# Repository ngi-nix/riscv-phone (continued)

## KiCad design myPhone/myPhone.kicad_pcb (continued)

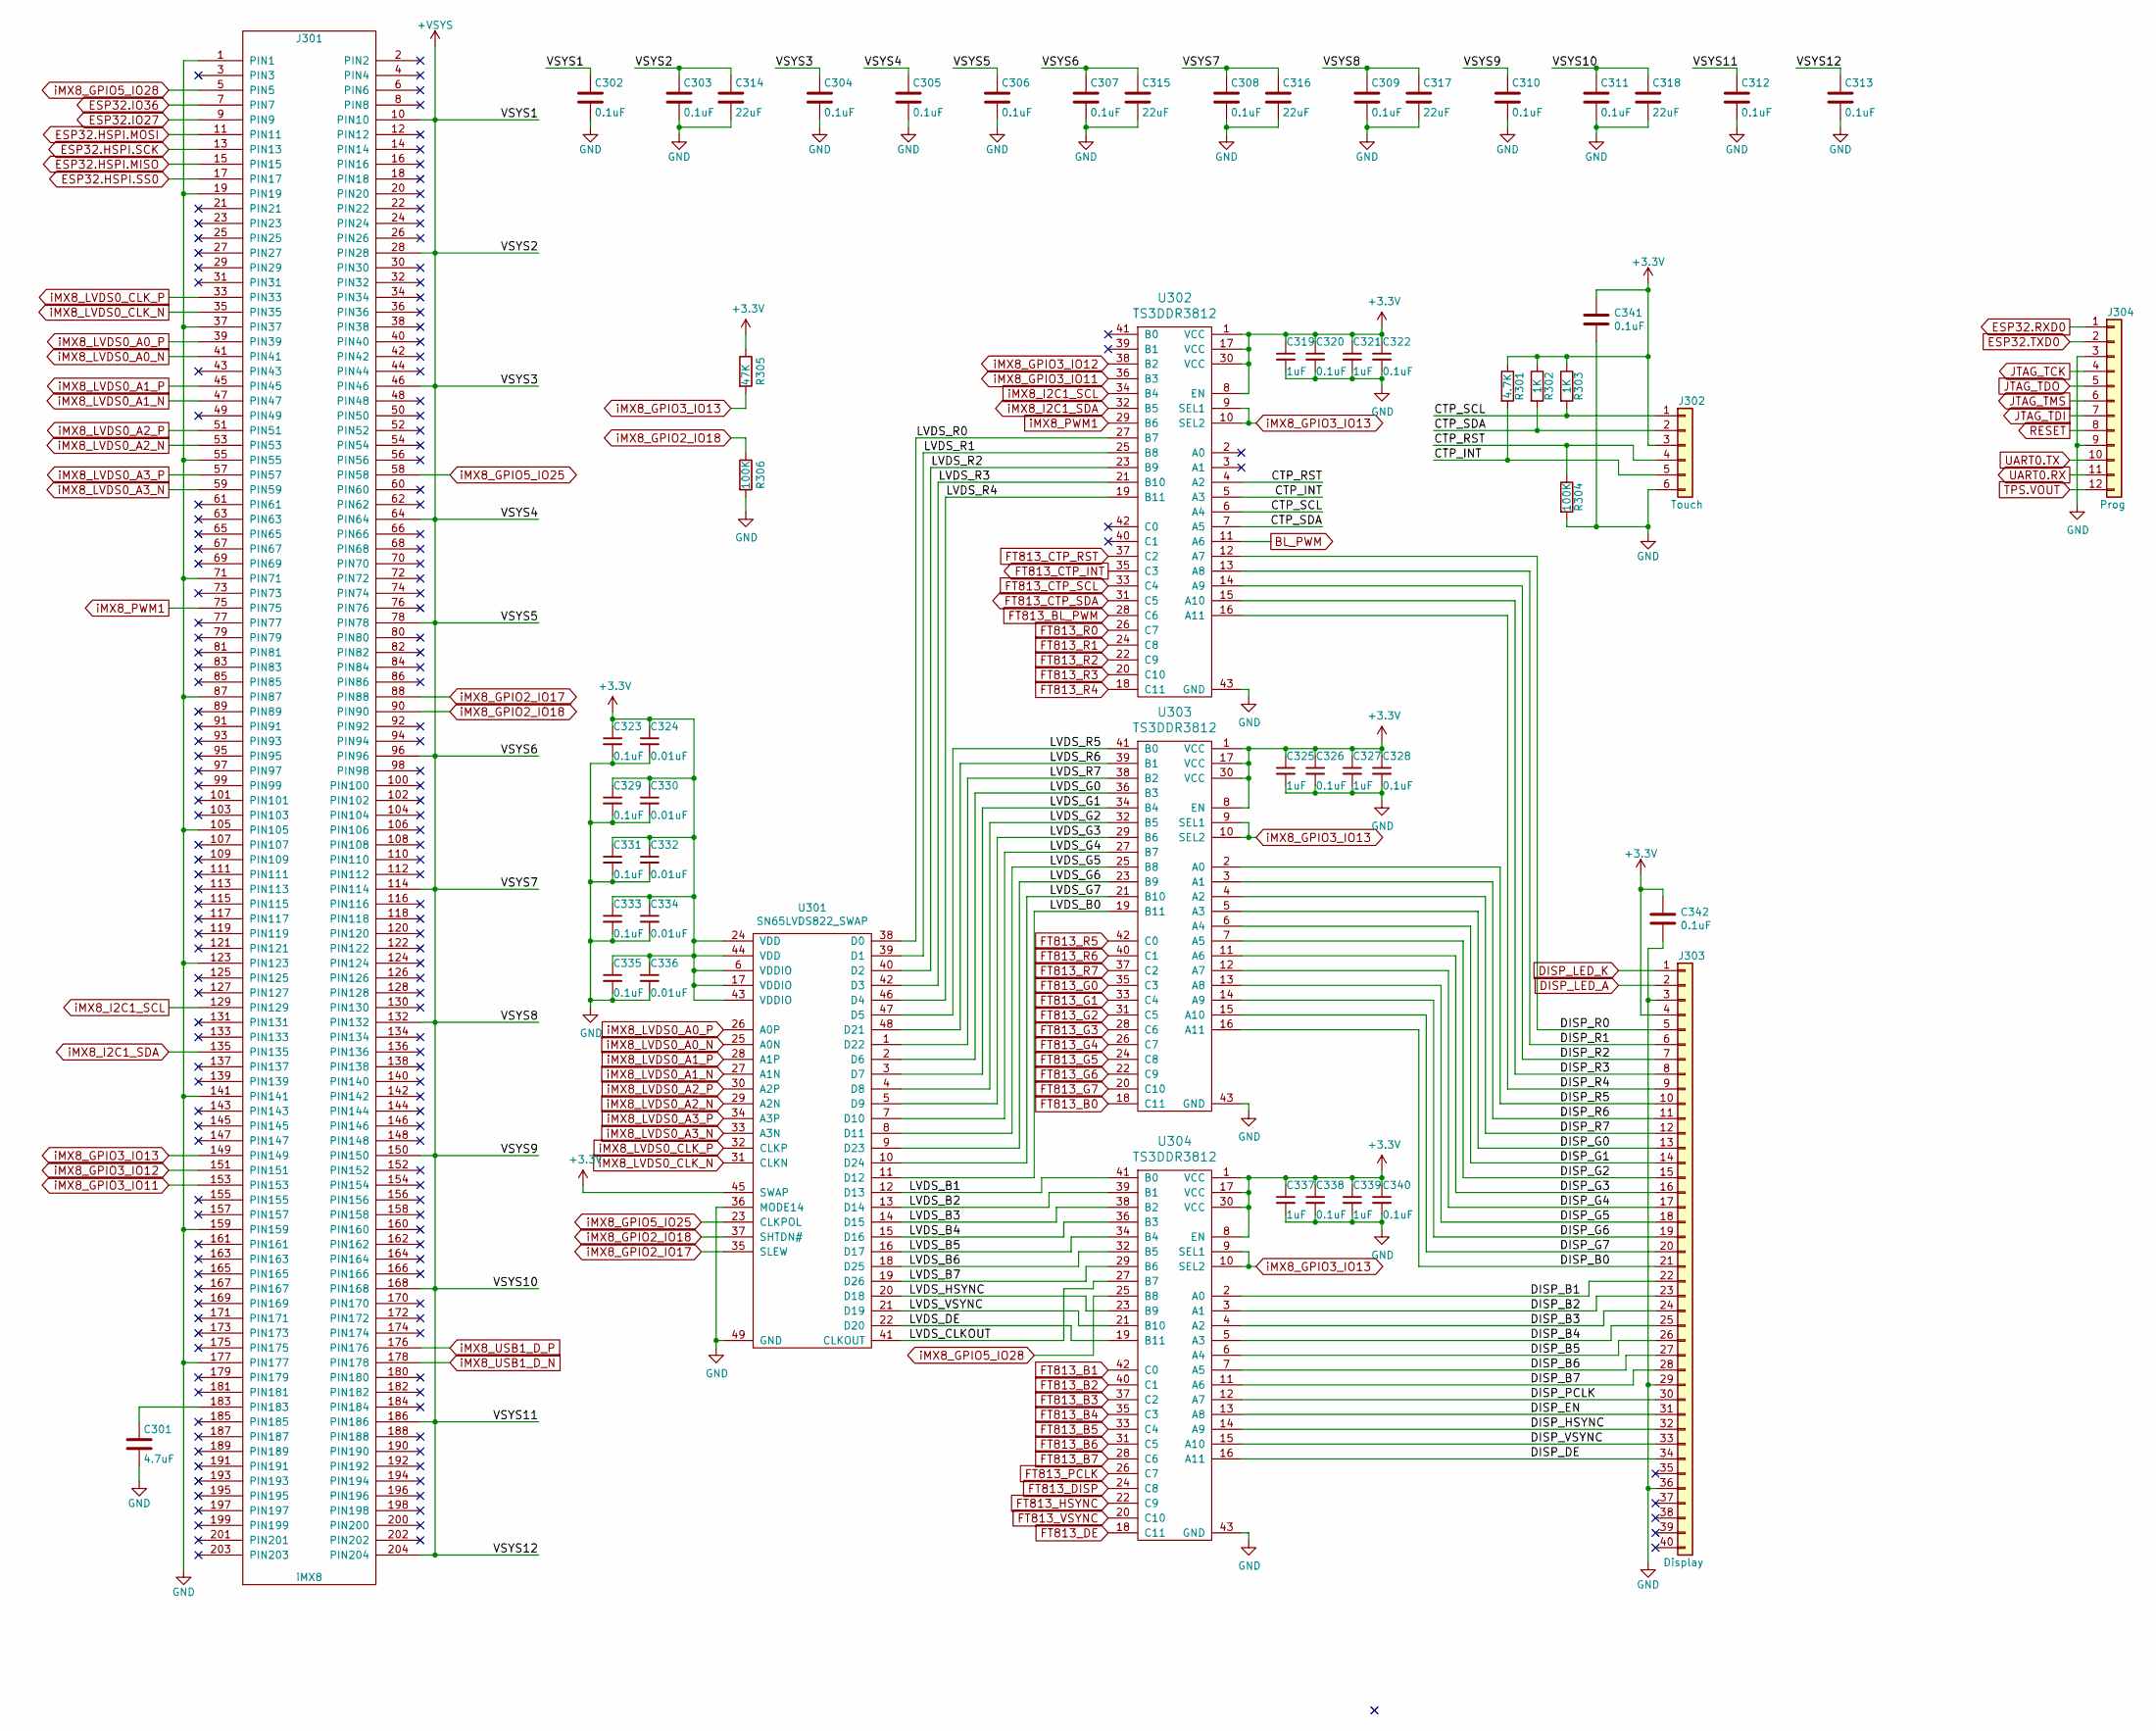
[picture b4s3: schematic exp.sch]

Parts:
C301: 4.7uF; C_0603_1608Metric
C302, C303, C304, C305, C306, C307, C308, C309, C310, C311, C312, C313, C320, C322, C323, C326, C328, C329, C331, C333, C335, C338, C340, C341, C342: 0.1uF; C_0603_1608Metric
C314, C315, C316, C317, C318: 22uF; C_0603_1608Metric
C319, C321, C325, C327, C337, C339: 1uF; C_0603_1608Metric
C324, C330, C332, C334, C336: 0.01uF; C_0603_1608Metric
J301: iMX8; Socket_SODIMM_DDR3_TE_2013289
J302: Touch; Hirose_FH12-6S-0.5SH_1x06-1MP_P0.50mm_Horizontal
J303: Display; Hirose_FH12-40S-0.5SH_1x40-1MP_P0.50mm_Horizontal
J304: Prog; Hirose_FH12-12S-0.5SH_1x12-1MP_P0.50mm_Horizontal
R301: 4.7K; R_0603_1608Metric
R302, R303: 1K; R_0603_1608Metric
R304, R306: 100K; R_0603_1608Metric
R305: 47K; R_0603_1608Metric
U301: SN65LVDS822_SWAP; QFN-48-1EP_7x7mm_P0.5mm_EP5.15x5.15mm_ThermalVias
U302, U303, U304: TS3DDR3812; Texas_R-PWQFN-N42

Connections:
+VSYS: C302.1, C303.1, C304.1, C305.1, C306.1, C307.1, C308.1, C309.1, C310.1, C311.1, C312.1, C313.1, C314.1, C315.1, C316.1, C317.1, C318.1, J301.10 (PIN10), J301.28 (PIN28), J301.46 (PIN46), J301.64 (PIN64), J301.78 (PIN78), J301.96 (PIN96), J301.114 (PIN114), J301.132 (PIN132), J301.150 (PIN150), J301.168 (PIN168), J301.186 (PIN186), J301.204 (PIN204); also elsewhere on the board
/exp/CTP_INT: J302.5, R301.2, U302.5 (A3)
/exp/CTP_RST: J302.4, R304.1, U302.4 (A2)
/exp/CTP_SCL: J302.1, R303.2, U302.6 (A4)
/exp/CTP_SDA: J302.2, R302.2, U302.7 (A5)
/exp/DISP_B0: J303.21, U303.16 (A11)
/exp/DISP_B1: J303.22, U304.2 (A0)
/exp/DISP_B2: J303.23, U304.3 (A1)
/exp/DISP_B3: J303.24, U304.4 (A2)
/exp/DISP_B4: J303.25, U304.5 (A3)
/exp/DISP_B5: J303.26, U304.6 (A4)
/exp/DISP_B6: J303.27, U304.7 (A5)
/exp/DISP_B7: J303.28, U304.11 (A6)
/exp/DISP_DE: J303.34, U304.16 (A11)
/exp/DISP_EN: J303.31, U304.13 (A8)
/exp/DISP_G0: J303.13, U303.5 (A3)
/exp/DISP_G1: J303.14, U303.6 (A4)
/exp/DISP_G2: J303.15, U303.7 (A5)
/exp/DISP_G3: J303.16, U303.11 (A6)
/exp/DISP_G4: J303.17, U303.12 (A7)
/exp/DISP_G5: J303.18, U303.13 (A8)
/exp/DISP_G6: J303.19, U303.14 (A9)
/exp/DISP_G7: J303.20, U303.15 (A10)
/exp/DISP_HSYNC: J303.32, U304.14 (A9)
/exp/DISP_PCLK: J303.30, U304.12 (A7)
/exp/DISP_R0: J303.5, U302.12 (A7)
/exp/DISP_R1: J303.6, U302.13 (A8)
/exp/DISP_R2: J303.7, U302.14 (A9)
/exp/DISP_R3: J303.8, U302.15 (A10)
/exp/DISP_R4: J303.9, U302.16 (A11)
/exp/DISP_R5: J303.10, U303.2 (A0)
/exp/DISP_R6: J303.11, U303.3 (A1)
/exp/DISP_R7: J303.12, U303.4 (A2)
/exp/DISP_VSYNC: J303.33, U304.15 (A10)
/exp/LVDS_B0: U301.11 (D12), U303.19 (B11)
/exp/LVDS_B1: U301.12 (D13), U304.41 (B0)
/exp/LVDS_B2: U301.13 (D14), U304.39 (B1)
/exp/LVDS_B3: U301.14 (D15), U304.38 (B2)
/exp/LVDS_B4: U301.15 (D16), U304.36 (B3)
/exp/LVDS_B5: U301.16 (D17), U304.34 (B4)
/exp/LVDS_B6: U301.18 (D25), U304.32 (B5)
/exp/LVDS_B7: U301.19 (D26), U304.29 (B6)
/exp/LVDS_CLKOUT: U301.41 (CLKOUT), U304.27 (B7)
/exp/LVDS_DE: U301.22 (D20), U304.19 (B11)
/exp/LVDS_G0: U301.2 (D6), U303.36 (B3)
/exp/LVDS_G1: U301.3 (D7), U303.34 (B4)
/exp/LVDS_G2: U301.4 (D8), U303.32 (B5)
/exp/LVDS_G3: U301.5 (D9), U303.29 (B6)
/exp/LVDS_G4: U301.7 (D10), U303.27 (B7)
/exp/LVDS_G5: U301.8 (D11), U303.25 (B8)
/exp/LVDS_G6: U301.9 (D23), U303.23 (B9)
/exp/LVDS_G7: U301.10 (D24), U303.21 (B10)
/exp/LVDS_HSYNC: U301.20 (D18), U304.23 (B9)
/exp/LVDS_R0: U301.38 (D0), U302.27 (B7)
/exp/LVDS_R1: U301.39 (D1), U302.25 (B8)
/exp/LVDS_R2: U301.40 (D2), U302.23 (B9)
/exp/LVDS_R3: U301.42 (D3), U302.21 (B10)
/exp/LVDS_R4: U301.46 (D4), U302.19 (B11)
/exp/LVDS_R5: U301.47 (D5), U303.41 (B0)
/exp/LVDS_R6: U301.48 (D21), U303.39 (B1)
/exp/LVDS_R7: U301.1 (D22), U303.38 (B2)
/exp/LVDS_VSYNC: U301.21 (D19), U304.21 (B10)
BL_PWM: U302.11 (A6); also elsewhere on the board
DISP_LED_A: J303.2; also elsewhere on the board
DISP_LED_K: J303.1; also elsewhere on the board
ESP32.HSPI.MISO: J301.15 (PIN15); also elsewhere on the board
ESP32.HSPI.MOSI: J301.11 (PIN11); also elsewhere on the board
ESP32.HSPI.SCK: J301.13 (PIN13); also elsewhere on the board
ESP32.HSPI.SS0: J301.17 (PIN17); also elsewhere on the board
ESP32.IO27: J301.9 (PIN9); also elsewhere on the board
ESP32.IO36: J301.7 (PIN7); also elsewhere on the board
ESP32.RXD0: J304.1; also elsewhere on the board
ESP32.TXD0: J304.2; also elsewhere on the board
FT813_B0: U303.18 (C11); also elsewhere on the board
FT813_B1: U304.42 (C0); also elsewhere on the board
FT813_B2: U304.40 (C1); also elsewhere on the board
FT813_B3: U304.37 (C2); also elsewhere on the board
FT813_B4: U304.35 (C3); also elsewhere on the board
FT813_B5: U304.33 (C4); also elsewhere on the board
FT813_B6: U304.31 (C5); also elsewhere on the board
FT813_B7: U304.28 (C6); also elsewhere on the board
FT813_BL_PWM: U302.28 (C6); also elsewhere on the board
FT813_CTP_INT: U302.35 (C3); also elsewhere on the board
FT813_CTP_RST: U302.37 (C2); also elsewhere on the board
FT813_CTP_SCL: U302.33 (C4); also elsewhere on the board
FT813_CTP_SDA: U302.31 (C5); also elsewhere on the board
FT813_DE: U304.18 (C11); also elsewhere on the board
FT813_DISP: U304.24 (C8); also elsewhere on the board
FT813_G0: U303.35 (C3); also elsewhere on the board
FT813_G1: U303.33 (C4); also elsewhere on the board
FT813_G2: U303.31 (C5); also elsewhere on the board
FT813_G3: U303.28 (C6); also elsewhere on the board
FT813_G4: U303.26 (C7); also elsewhere on the board
FT813_G5: U303.24 (C8); also elsewhere on the board
FT813_G6: U303.22 (C9); also elsewhere on the board
FT813_G7: U303.20 (C10); also elsewhere on the board
FT813_HSYNC: U304.22 (C9); also elsewhere on the board
FT813_PCLK: U304.26 (C7); also elsewhere on the board
FT813_R0: U302.26 (C7); also elsewhere on the board
FT813_R1: U302.24 (C8); also elsewhere on the board
FT813_R2: U302.22 (C9); also elsewhere on the board
FT813_R3: U302.20 (C10); also elsewhere on the board
FT813_R4: U302.18 (C11); also elsewhere on the board
FT813_R5: U303.42 (C0); also elsewhere on the board
FT813_R6: U303.40 (C1); also elsewhere on the board
FT813_R7: U303.37 (C2); also elsewhere on the board
FT813_VSYNC: U304.20 (C10); also elsewhere on the board
GND: C301.2, C302.2, C303.2, C304.2, C305.2, C306.2, C307.2, C308.2, C309.2, C310.2, C311.2, C312.2, C313.2, C314.2, C315.2, C316.2, C317.2, C318.2, C319.2, C320.2, C321.2, C322.2, C323.2, C324.2, C325.2, C326.2, C327.2, C328.2, C329.2, C330.2, C331.2, C332.2, C333.2, C334.2, C335.2, C336.2, C337.2, C338.2, C339.2, C340.2, C341.2, C342.2, J301.1 (PIN1), J301.19 (PIN19), J301.37 (PIN37), J301.55 (PIN55), J301.71 (PIN71), J301.87 (PIN87), J301.105 (PIN105), J301.123 (PIN123), J301.141 (PIN141), J301.159 (PIN159), J301.177 (PIN177), J302.6, J303.3, J303.29, J303.36, J304.3, J304.9, R304.2, R306.2, U301.36 (MODE14), U301.49 (GND), U302.43 (GND), U303.43 (GND), U304.43 (GND); also elsewhere on the board
JTAG_TCK: J304.4; also elsewhere on the board
JTAG_TDI: J304.7; also elsewhere on the board
JTAG_TDO: J304.5; also elsewhere on the board
JTAG_TMS: J304.6; also elsewhere on the board
unnamed: C301.1, J301.183 (PIN183)
RESET: J304.8; also elsewhere on the board
TPS.VOUT: J304.12; also elsewhere on the board
UART0.RX: J304.11; also elsewhere on the board
UART0.TX: J304.10; also elsewhere on the board
iMX8_GPIO2_IO17: J301.88 (PIN88), U301.35 (SLEW)
iMX8_GPIO2_IO18: J301.90 (PIN90), R306.1, U301.37 (SHTDN#)
iMX8_GPIO3_IO11: J301.153 (PIN153), U302.36 (B3)
iMX8_GPIO3_IO12: J301.151 (PIN151), U302.38 (B2)
iMX8_GPIO3_IO13: J301.149 (PIN149), R305.2, U302.9 (SEL1), U302.10 (SEL2), U303.9 (SEL1), U303.10 (SEL2), U304.9 (SEL1), U304.10 (SEL2)
iMX8_GPIO5_IO25: J301.58 (PIN58), U301.23 (CLKPOL)
iMX8_GPIO5_IO28: J301.5 (PIN5), U304.25 (B8)
iMX8_I2C1_SCL: J301.129 (PIN129), U302.34 (B4)
iMX8_I2C1_SDA: J301.135 (PIN135), U302.32 (B5)
iMX8_LVDS0_A0_N: J301.41 (PIN41), U301.25 (A0N)
iMX8_LVDS0_A0_P: J301.39 (PIN39), U301.26 (A0P)
iMX8_LVDS0_A1_N: J301.47 (PIN47), U301.27 (A1N)
iMX8_LVDS0_A1_P: J301.45 (PIN45), U301.28 (A1P)
iMX8_LVDS0_A2_N: J301.53 (PIN53), U301.29 (A2N)
iMX8_LVDS0_A2_P: J301.51 (PIN51), U301.30 (A2P)
iMX8_LVDS0_A3_N: J301.59 (PIN59), U301.33 (A3N)
iMX8_LVDS0_A3_P: J301.57 (PIN57), U301.34 (A3P)
iMX8_LVDS0_CLK_N: J301.35 (PIN35), U301.31 (CLKN)
iMX8_LVDS0_CLK_P: J301.33 (PIN33), U301.32 (CLKP)
iMX8_PWM1: J301.75 (PIN75), U302.29 (B6)
iMX8_USB1_D_N: J301.178 (PIN178); also elsewhere on the board
iMX8_USB1_D_P: J301.176 (PIN176); also elsewhere on the board

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
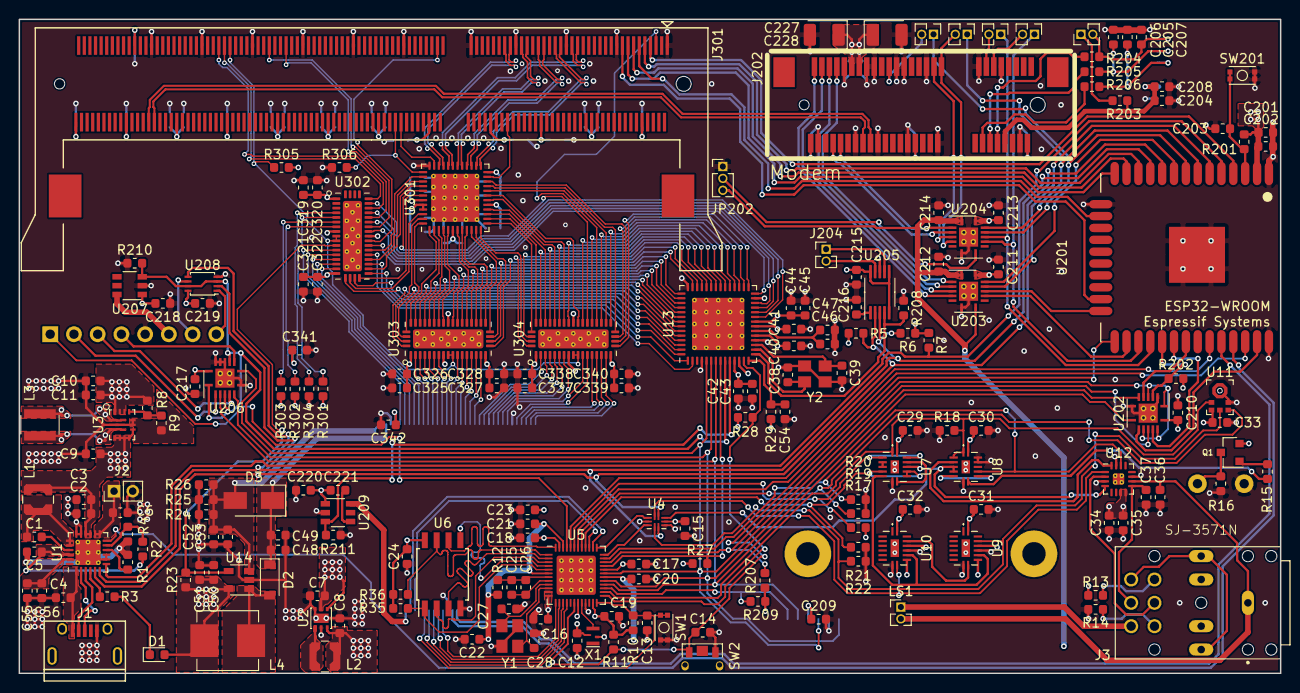
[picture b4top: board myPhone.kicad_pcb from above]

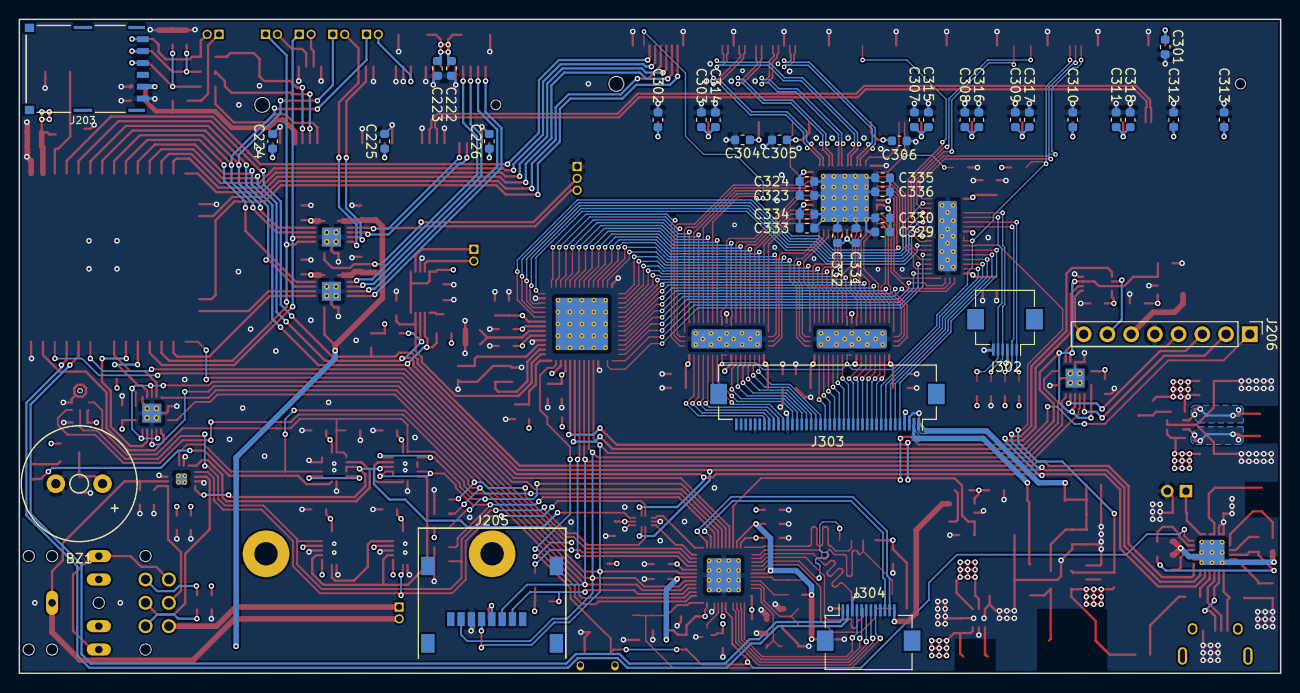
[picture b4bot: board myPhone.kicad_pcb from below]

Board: 4 copper layers, 135.0 x 70.0 mm, 235 parts (40 on the bottom side), 259 nets.

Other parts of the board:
C15: 0.1uF; C_0603_1608Metric
C55, C56: 22uF; C_0603_1608Metric
U4: TMUX154E; UQFN-10_1.3x1.8mm_P0.4mm

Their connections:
/SPK_EN: U4.10; also elsewhere on the board
GND: C15.2, C55.2, C56.2, U4.4, U4.8; also elsewhere on the board
unnamed 176: C55.1, C56.1; also elsewhere on the board
TMUX.I2C0.SCL: U4.1; also elsewhere on the board
TMUX.I2C0.SDA: U4.7; also elsewhere on the board

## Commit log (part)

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2020-02-26 ecp/eos new compatibility changes
2020-02-26 spidev set divider
2020-02-26 fixed build system
2020-02-26 text widget added, NOT TESTED
2020-03-07 fixed sbrk
2020-03-07 eve screen/tile/canvas/page/form fw added; page widget added
2020-03-07 fixed build sys
2020-03-11 timer fix
2020-05-06 at cmd processing; pppos driver
2020-05-09 added sleep/wake for modem; fixed ppp driver API
2020-05-09 fixed wifi driver
2020-05-09 wifi driver fix
2020-05-17 power management implemented; net protocol change
2020-05-17 power management fix
2020-05-18 poer management fix
2020-05-23 esp32 deep sleep implemented
2020-05-26 added license
2020-05-26 added license files
2020-06-06 ecp_timer_retry_t typedef fixed
2020-06-06 ecp_conn_handler_new_t typedef fixed
2020-06-06 ecp_conn_handler_msg_t typedef fixed
2020-06-06 ecp_conn_alloc_t/ecp_conn_free_t typedefs fixed
2020-06-06 ecp_conn_create_t/ecp_conn_destroy_t/ecp_conn_open_t/ecp_conn_close_t typedefs fixed
2020-06-08 touch extended tracking refactor
2020-06-08 kbd iface fixed
2020-06-08 EVEView iface fixed; screen keyboard window implemented
2020-06-11 added widget labels
2020-06-11 implemented font metrics
2020-06-25 extendend events implemented for touch
2020-06-25 text widget fixed
2020-07-02 string widget implemented
2020-07-02 string init/draw implemented; page to screen coordinates implemented
2020-07-03 str widget draw selection and cursor implemented
2020-07-11 screen/window/kbd window implemented; str widget tested
2020-07-11 kbdwin source added
2020-07-11 page focus interface changed; widget is responsible for setting focus
2020-07-11 String copy/paste implemented
2020-08-03 unicode verify fixed
2020-08-03 unicode moved
2020-08-04 added tmux lib
2020-08-04 renamed to rvPhone
2020-08-05 unicode seek fix
2020-08-05 cell message type support
2020-08-05 new directory sructure for fe310 fw
2020-08-05 cell urc buffer handling fixed; added sms/ussd/voice/data stubs
2020-08-05 unicode support added
2020-08-05 ecp moved to root; fixed utils and tests
2020-08-05 code -> fw
2020-08-05 fixed modem test example
2020-08-07 net driver: removed obsolete flags; urc process simplefied; pcm: added active flag; tested cell voice/data
2020-08-07 added cell message types
2020-08-09 sms service added/tested
2020-08-09 unicode utf_len added; cell sms services added
2020-08-09 message handling iface updated
2020-08-09 uart dirty property added
2020-08-09 sms send wait for prompt
2020-08-09 added new sms flags
2020-08-09 sms storage flash mem
2020-08-09 support for sms flags
2020-08-11 cell messages are handled in separate task
2020-08-23 dynamic memory alloc for gui added; page navigation added
2020-08-24 fixed bug in form constructor; free widget improved
2020-08-26 display list burst mode added
2020-08-26 kbdwin removed; stack and contructor moved to view
2020-08-26 modem test application appified
2020-12-04 stereo audio out; lvds display; LSM9DS1 added
2021-02-24 i2c driver initial import
2021-02-24 added test app with voice, wifi/cellular data connectivity examples
2021-02-24 upgraded to esp-idf 4.2
2021-02-26 widgets are excluded from touch events when form gesture is in progress
2021-02-26 selectw verifies add/set options; implemented multi select
2021-02-26 fixed tag opts for string and text widget
2021-02-27 wifi scan verifies length of ssid
2021-02-27 cell/wifi refactoring
2021-02-28 net send will do selected spi dev pause/resume if more is set and netowk is not active
2021-02-28 font property moved to widget base
2021-02-28 refacotr app/ api
2021-02-28 added app form
2021-03-16 init code cleanup
2021-03-23 form scroll completed
2021-03-24 window hierarchy
2021-03-25 uievt added to view
2021-03-28 fixed cursor handling in strw and textw
2021-03-28 removed ext event tap1
2021-03-29 added display adapter for focuslcds E50RG84885LWAM520-CA panel
2021-03-29 added panel for rev2 board
2021-03-29 added missing footprints
2021-03-29 added CHANGES file
2021-03-29 renamed footprints
2021-03-29 added readme and licence files
2021-03-29 moved i2c from esp32 to fe310. added bq25895, drv2605 and lsm9ds1 i2c support
2021-04-08 added board.h
2021-04-08 reintrodiced spi_dev
2021-04-10 sdcard init fixed
2021-04-10 added gpio management
2021-04-10 i2c refactor
2021-05-10 added support for eve cmd loadimage and similar
2021-05-10 spi_dev: deselect not mandatory prior to select
2021-05-20 string widget update added
2021-05-20 initial touch calibration fixed
2021-05-20 fat filesystem with disk encryption for sd card driver
2021-05-20 net protocol added req/rep messages
2021-05-20 camera test app
2021-05-20 test app template
2021-08-06 fixed imx-boot
2021-08-06 fixed u-boot
2021-08-07 added kernel dts
2021-08-07 no usb for u-boot
2021-08-07 fixed dts
2021-08-07 added common.[ch] to u-boot
2021-08-17 adjusted ddr votages
2021-08-18 default governor is conservative
2021-08-18 added escp1 to dts
2021-08-19 spidev fix
2021-08-26 fixed lvds resolution
2021-08-27 fixed spid
2021-08-27 test app prints bq25895 regs
2021-08-27 net driver fixed
2021-08-27 fixed bq25895 initial regs
2021-08-27 temp commit for merge
2021-08-27 added missing components/footprints
2021-08-27 yocto rename
2021-08-29 ecp code cleanup
2021-08-31 transient messages added; code cleanup
2021-08-31 directory service added
2021-09-01 updated directory service
2021-10-01 HW REV 3.0
2021-10-01 updated CHANGES
2021-11-16 board REV3 pins in board.h; eve BT817 support
2021-11-17 wakeup cause added to init functions
2021-11-25 i2s init/start/running fixed; i2c start returns error if i2s is running
2021-11-25 spi display driver initial commit
2021-11-28 added pull-up pull-dn resistors; fixed input power;
2021-11-30 startup code uses init/run
2021-12-01 i2c added 16 bit register read/write
2021-12-07 fixed eve, spi start/stop interface
2021-12-09 improved init process
2021-12-23 fixed typo
2022-01-30 hashtable fix
2022-01-30 code cleanup and fixes mainly rbuf
2022-01-30 fixed build
2022-01-31 fixed rbuf
2022-01-31 build fix
2022-01-31 added libressl
2022-02-02 fixed new crypto
2022-02-02 renamed crypto -> ext
2022-02-02 moved aes sha and blowfish to crypto
2022-02-02 moved ecp, platform -> src
2022-02-02 tests fixed
2022-02-02 build fixed
2022-02-02 fsfat moved to ext dir
2022-02-02 move
2022-03-12 new rev compile OK
2022-03-12 dir/ext source files moved
2022-03-15 added thd locks for dir server
2022-03-15 added dir Makefile
2022-03-21 i2s stereo driver
2022-03-30 sock api fixed; net reply messages fixed
2022-03-31 vconn bugfix
2022-03-31 fe310 tests fixed
2022-04-02 connection table search fix; release packet buffer before send for vconn
2022-04-07 cookie gen/verify added
2022-04-08 connection exire added
2022-04-08 added missing header
2022-04-08 added AES to crypto library
2022-08-03 built fe310 firmware
2022-08-04 fixed test build
2022-08-05 adds a derivation that compiles the driver flake output. Co-authored-by: DieracDelta justin@restivo.me
2022-08-05 adds .a, result files to gitignore.
2022-08-05 Changing compiler to be 32 bit both in the flake and makefile, fixes #2.
2022-08-08 temporary fix while [PR](https://github.com/NixOS/nixpkgs/pull/182187) isn't merged, fixes #5.
2022-08-08 temporary fix while https://github.com/NixOS/nixpkgs/pull/182187 isn't merged, fixes #5.
2022-08-08 adds newlib-nano variant to platform configuration.
2022-08-08 added comment
2022-08-10 trying out paths for nano libraries.
2022-08-10 added newlib-nano to buildInputs.
2022-08-10 cleaned up some unecessary lines.
2022-08-10 copied and renamed nano libraries manually, added back compiler.
2022-08-11 feeds newlib archives to compiler, fixes #4
2022-08-12 magic combination of flags that seem to fix #6
2022-08-12 commented out line since app_test doesn't exist, fixes #7
2022-08-12 removing unecessary binutils and newlib-nano declaration.
2022-08-12 added a postInstall phase, symlinks and renames newlib-nano archive files.
2022-08-12 uncommented the checkPhase.
2022-08-12 unfolded packages attribute.
2022-08-12 esp32 firmware build scaffolding.
2022-08-12 unecessary environmental variable.
2022-08-12 added newlines.
2022-08-12 renamed the shell designation for fe310.
2022-08-14 uncomment line, fw/fe310/test/test.c isn't empty after all.
2022-08-14 removes all archive files created previously.
2022-08-14 fixes indentation
2022-08-14 this branch concerns only the firmware for the fe310.
2022-08-16 flake-based, nix develop replaces nix-shell
2022-08-16 directory nanolib replaces $out as it's less confusing
2022-08-17 move shell hook script to the let section
2022-08-17 add package openocd
2022-08-18 write script to the store and make executable.
2022-08-19 wrap nanolibs script.
2022-08-19 build and run nanolibsPath derivation.
2022-08-19 cleanup, newlines, blank spaces
2022-08-19 moves the shell script to its own file
2022-08-23 string interpolation won't work from an external file through builtins.readFile
2022-08-29 remove option to pass 64-bit floating-point arguments
2022-08-30 Updates flake lock.
2022-09-07 add: esp32-toolchain
2022-09-07 pin nixpkgs for compatibility with nixpkgs-dev-esp
    The `nixpkgs` revision is pinned to the version that is specified in
    `nixpkgs-dev-esp`, because it is compatible with the referenced
    `mach-nix` revision.
    See: https://github.com/mirrexagon/nixpkgs-esp-dev/issues/10#issuecomment-1193227845
2022-09-07 add: outputs
2022-09-07 bind the callPackage pattern
2022-09-10 Got rid of flake-utils, refactored accordingly.
2022-09-10 Updated lock file, removed flake-utils.
2022-09-15 Removes unecessary input.
2022-09-15 Remove command as it won't run inside derivation.
2022-09-15 Creates a build directory in $out.
2022-09-15 Creates a test directory in $out.
2022-09-15 Moves the test object files into the build directory at $out.
2022-09-15 Removes the custom checkPhase.
2022-09-15 Moves NANOLIBS_PATH environment variable setting out from the preBuild phase.
2022-09-15 Adds the nanolibsPath derivation to the buildInputs.
2022-09-15 Executes the script nanolibs-path before compile time.
2022-09-15 Executes the makefile in the fw/fe310/test directory.
2022-09-15 Copy all object files into $out, then those in fw/fe310/test.
2022-09-16 Added documentation.
2022-09-16 Renamed the fe310 derivation.
2022-09-16 Add openocd as a build input.
2022-09-16 Added documentation concerning the developer shell usage.
2022-09-16 RISCV_HOME and RISCV_OPENOCD_HOME required by fw/fe310/Makefile, line 29.
2022-09-16 Updated TODO.
2022-09-16 Compile the test object files only, don't run the upload script.
2022-09-16 Updated lock file.
2022-09-16 Exposes upstream repository.
2022-09-16 removed copy of upstream repository.
2022-09-16 When entering the developer shell, cd into $src automatically.
2022-09-16 We now grab source files from upstream, update $src accordingly.
2022-09-16 Replace 32-bit with 64-bit instruction set.
2022-09-16 Remove uncessary lines.
2022-09-16 Find and replace string with tuple that we can find.
2022-09-16 make in the right directory.
2022-09-16 find compiled files and move them in one stroke.
2022-09-16 add and update documentation.
2022-09-16 Wrap dependencies within a single input schema.
2022-09-17 update TODO.
2022-09-17 removes TODO.
2022-09-17 adds actual content to the README file.
2022-09-17 Squashed commit of the following:
    commit 19e87a01ec48e02937d59885266060acd092e773
    Author: nuno <info@nunopedrosa.net>
    Date: Sat Sep 17 21:37:46 2022 +0100
    mob next [ci-skip] [ci skip] [skip ci]
    lastFile:flake.nix
    commit 80325e23ad527fe4a7750462337f01a8b16d4bc3
2022-09-19 mob next [ci-skip] [ci skip] [skip ci]
    lastFile:flake.nix
2022-09-19 mob next [ci-skip] [ci skip] [skip ci]
    lastFile:TODO.md
2022-09-21 mob next [ci-skip] [ci skip] [skip ci]
2022-09-21 mob next [ci-skip] [ci skip] [skip ci]
    lastFile:nanolibs.nix
2022-09-22 mob next [ci-skip] [ci skip] [skip ci]
    lastFile:fe310.nix
2022-09-24 mob next [ci-skip] [ci skip] [skip ci]
    lastFile:esp32.nix
2022-09-24 mob next [ci-skip] [ci skip] [skip ci]
    lastFile:.gitignore
